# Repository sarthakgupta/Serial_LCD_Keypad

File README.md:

5 wire interface of LCD and keypad 
==================================

I have used 2 serial 8-bit shift registers(74hct595), which takes serial data, latch clock and serial clock, on giving them 8-bit serial data we can have 8- bit parallel data out of 74hct595, when these two shift registers are placed in cascade manner (you can refer schematic) we can have 16- bit parallel data from 16-bit serial input. I have used keypad in 8x2 format so I need 8 data lines as input to keypad and will be having 2 data lines as output from keypad. When LCD is used in 4-bit mode we need 6 data lines (D4,D5,D6,D7,RS,EN).So I require 3 data lines for shift registers and 2 data lines for keypad, thus 5 data lines to control LCD and Keypad. I have demonstrated it with Arduino Uno and also on the Arduino based protoboard("LOLduino"). It works even if your controller works at 3.3V, because when you give input as 5V to the Vcc of the shift registers, it take 3.3V as high logic.

Cheers!!

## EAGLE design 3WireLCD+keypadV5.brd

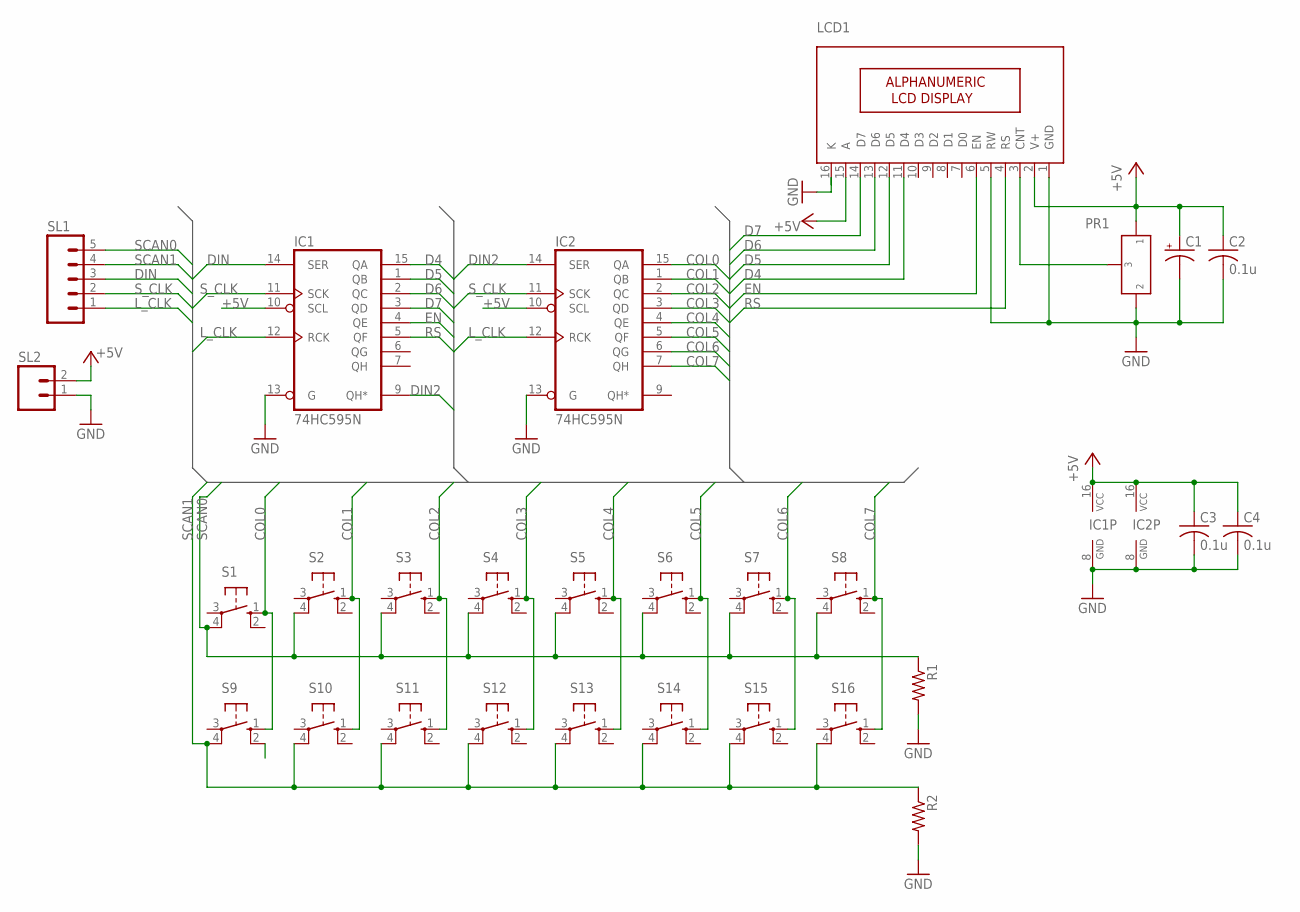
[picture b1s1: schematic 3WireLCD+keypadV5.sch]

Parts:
C1: CAP_POL_16V; B/3528-21R
C2, C3, C4: 0.1u; C0805
IC1, IC2: 74HC595N; DIL16
LCD1: 16X2LCD; 16X2_LCD
R1, R2: RESISTOR0805; R0805
S1, S2, S3, S4, S5, S6, S7, S8, S9, S10, S11, S12, S13, S14, S15, S16: 40-XX; B3F-40XX
SL1: M05; 05P
SL2: M02; 02P
U$1: PRESET; PRESET_PACK

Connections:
+5V: C1.+, C2.1, C3.1, C4.1, IC1.10 (SCL), IC1.16 (VCC), IC2.10 (SCL), IC2.16 (VCC), LCD1.2 (V+), LCD1.15 (A), SL2.2, U$1.P$1 (1)
COL0: IC2.15 (QA), S1.1 (S), S9.1 (S)
COL1: IC2.1 (QB), S2.1 (S), S10.1 (S)
COL2: IC2.2 (QC), S3.1 (S), S11.1 (S)
COL3: IC2.3 (QD), S4.1 (S), S12.1 (S)
COL4: IC2.4 (QE), S5.1 (S), S13.1 (S)
COL5: IC2.5 (QF), S6.1 (S), S14.1 (S)
COL6: IC2.6 (QG), S7.1 (S), S15.1 (S)
COL7: IC2.7 (QH), S8.1 (S), S16.1 (S)
D4: IC1.15 (QA), LCD1.11 (D4)
D5: IC1.1 (QB), LCD1.12 (D5)
D6: IC1.2 (QC), LCD1.13 (D6)
D7: IC1.3 (QD), LCD1.14 (D7)
DIN: IC1.14 (SER), SL1.3
DIN2: IC1.9 (QH*), IC2.14 (SER)
EN: IC1.4 (QE), LCD1.6 (EN)
GND: C1.-, C2.2, C3.2, C4.2, IC1.8 (GND), IC1.13 (G), IC2.8 (GND), IC2.13 (G), LCD1.1 (GND), LCD1.5 (RW), LCD1.16 (K), R1.2, R2.2, SL2.1, U$1.P$2 (2)
L_CLK: IC1.12 (RCK), IC2.12 (RCK), SL1.1
unnamed: LCD1.3 (CNT), U$1.P$3 (3)
RS: IC1.5 (QF), LCD1.4 (RS)
SCAN0: R1.1, S1.4 (P1), S2.4 (P1), S3.4 (P1), S4.4 (P1), S5.4 (P1), S6.4 (P1), S7.4 (P1), S8.4 (P1), SL1.5
SCAN1: R2.1, S9.4 (P1), S10.4 (P1), S11.4 (P1), S12.4 (P1), S13.4 (P1), S14.4 (P1), S15.4 (P1), S16.4 (P1), SL1.4
S_CLK: IC1.11 (SCK), IC2.11 (SCK), SL1.2

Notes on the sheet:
PR1

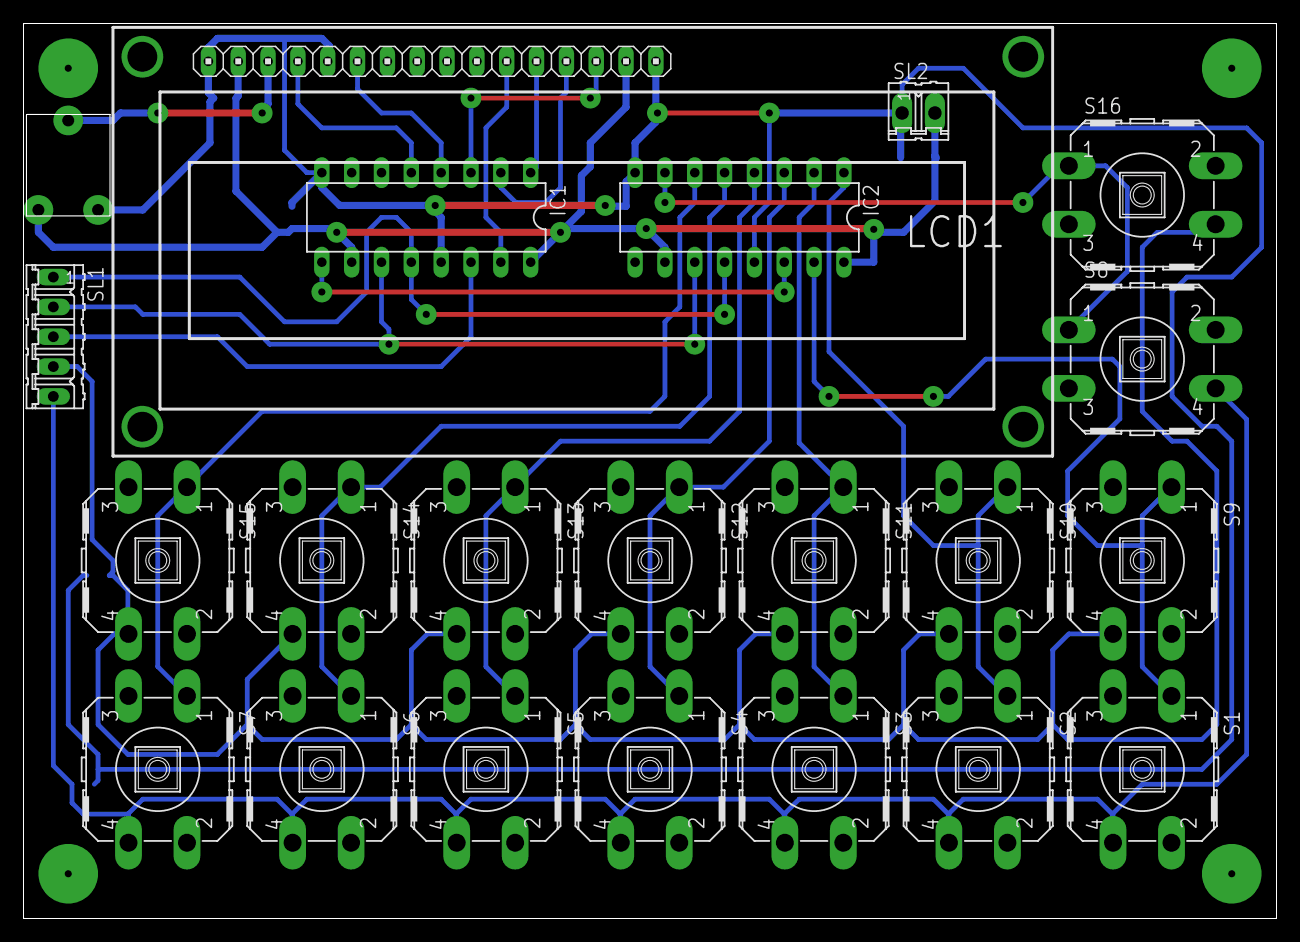
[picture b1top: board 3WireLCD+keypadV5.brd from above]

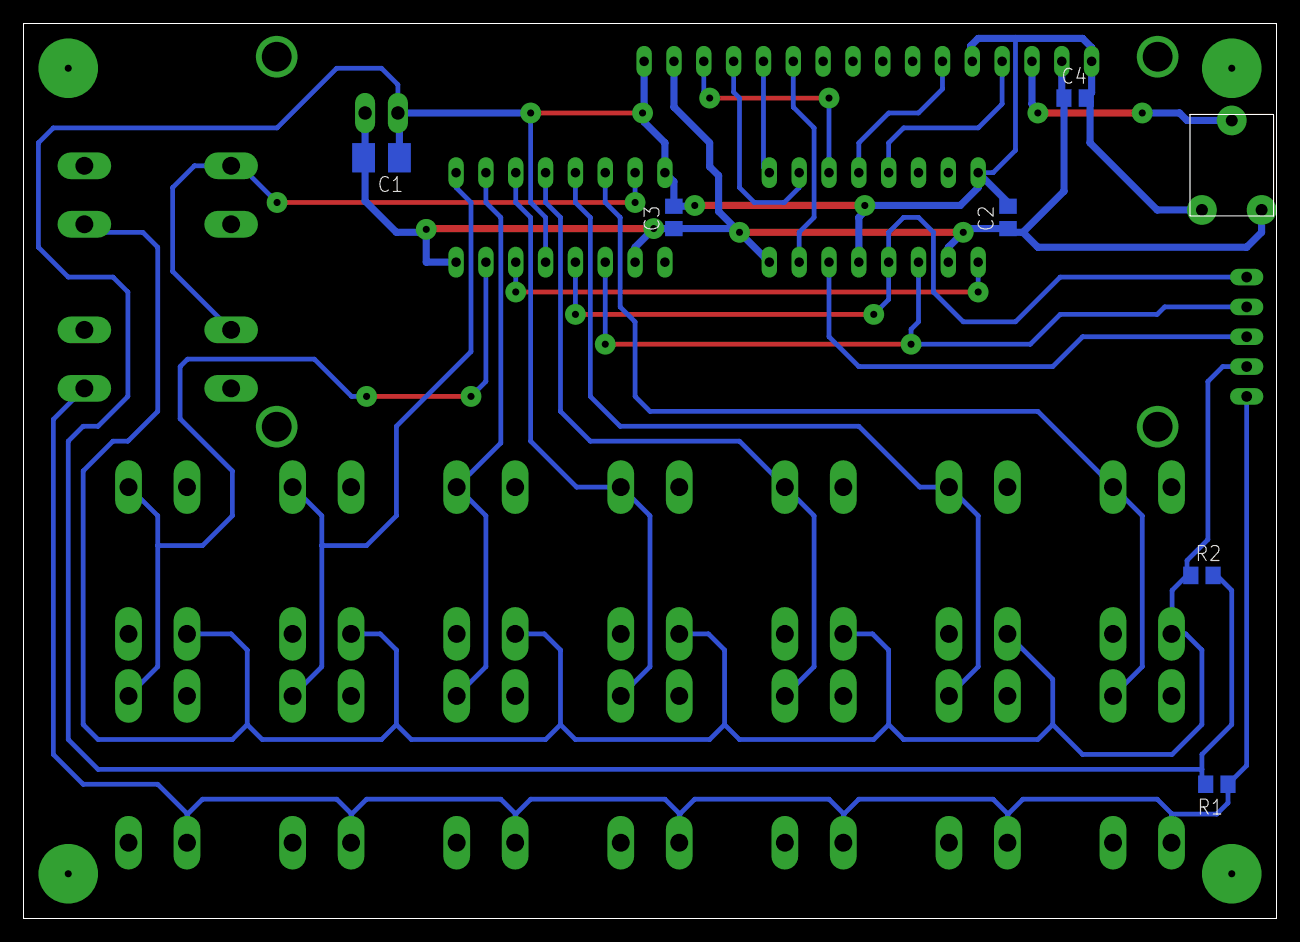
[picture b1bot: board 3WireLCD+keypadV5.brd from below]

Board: 2 copper layers, 106.7 x 76.2 mm, 28 parts (6 on the bottom side), 23 nets.

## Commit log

2013-12-01 3 wire serial LCD and Keypad
2013-12-01 read me
2013-12-01 updated ream me
